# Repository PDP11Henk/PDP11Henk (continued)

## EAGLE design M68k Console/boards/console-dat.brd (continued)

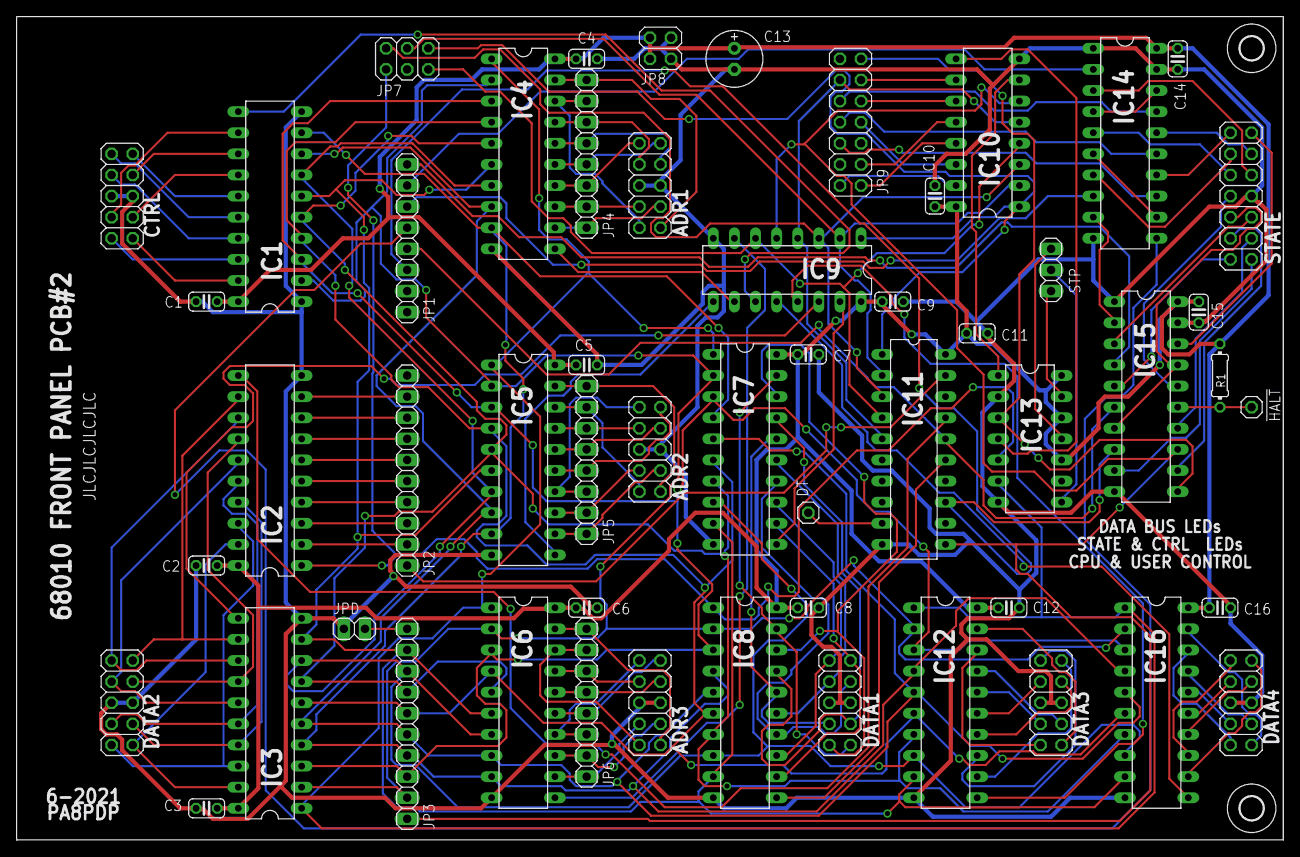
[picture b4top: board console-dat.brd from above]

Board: 2 copper layers, 152.4 x 99.1 mm, 57 parts (0 on the bottom side), 141 nets.

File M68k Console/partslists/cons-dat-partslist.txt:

Partlist

Exported from console-dat.sch at 14-6-2021 21:06

EAGLE Version 7.6.0 Copyright (c) 1988-2016 CadSoft

Assembly variant: 

Part     Value          Device          Package      Library  Sheet

!HALT    !HALT          PINHD-1X1       1X01         pinhead  4
ADR1     ADR1           PINHD-2X5       2X05         pinhead  4
ADR2     ADR2           PINHD-2X5       2X05         pinhead  4
ADR3     ADR3           PINHD-2X5       2X05         pinhead  4
C1       100n           C-EU025-024X044 C025-024X044 rcl      2
C2       100n           C-EU025-024X044 C025-024X044 rcl      2
C3       100n           C-EU025-024X044 C025-024X044 rcl      2
C4       100n           C-EU025-024X044 C025-024X044 rcl      2
C5       100n           C-EU025-024X044 C025-024X044 rcl      2
C6       100n           C-EU025-024X044 C025-024X044 rcl      2
C7       100n           C-EU025-024X044 C025-024X044 rcl      2
C8       100n           C-EU025-024X044 C025-024X044 rcl      2
C9       100n           C-EU025-024X044 C025-024X044 rcl      2
C10      100n           C-EU025-024X044 C025-024X044 rcl      1
C11      220n           C-EU025-024X044 C025-024X044 rcl      2
C12      100n           C-EU025-024X044 C025-024X044 rcl      2
C13      470µF          CPOL-EUE2.5-7   E2,5-7       rcl      1
C14      100n           C-EU025-024X044 C025-024X044 rcl      2
C15      100n           C-EU025-024X044 C025-024X044 rcl      2
C16      100n           C-EU025-024X044 C025-024X044 rcl      2
CTRL     CTRL           PINHD-2X5       2X05         pinhead  4
DATA1    DATA1          PINHD-2X5       2X05         pinhead  2
DATA2    DATA2          PINHD-2X5       2X05         pinhead  2
DATA3    DATA3          PINHD-2X5       2X05         pinhead  2
DATA4    DATA4          PINHD-2X5       2X05         pinhead  2
DT       DT             PINHD-1X1       1X01         pinhead  1
IC1      74HCT574N      74HCT574N       DIL20        74xx-eu  4
IC2      74HCT574N      74HCT574N       DIL20        74xx-eu  2
IC3      74HCT574N      74HCT574N       DIL20        74xx-eu  2
IC4      74HCT574N      74HCT574N       DIL20        74xx-eu  4
IC5      74HCT574N      74HCT574N       DIL20        74xx-eu  4
IC6      74HCT574N      74HCT574N       DIL20        74xx-eu  4
IC7      74HCT574N      74HCT574N       DIL20        74xx-eu  2
IC8      74HCT574N      74HCT574N       DIL20        74xx-eu  2
IC9      74LS138N       74LS138N        DIL16        74xx-eu  3
IC10     74LS138N       74LS138N        DIL16        74xx-eu  3
IC11     ATF16V8BP3     ATF16V8BP3      DIL20        atmel    3
IC12     74HCT574N      74HCT574N       DIL20        74xx-eu  2
IC13     74LS74N        74LS74N         DIL14        74xx-eu  3
IC14     74LS240N       74LS240N        DIL20        74xx-eu  4
IC15     74LS240N       74LS240N        DIL20        74xx-eu  4
IC16     74HCT574N      74HCT574N       DIL20        74xx-eu  2
JP1      JP1            PINHD-1X8       1X08         pinhead  1
JP2      JP2            PINHD-1X10      1X10         pinhead  1
JP3      JP3            PINHD-1X10      1X10         pinhead  1
JP4      JP4            PINHD-1X8       1X08         pinhead  1
JP5      JP5            PINHD-1X8       1X08         pinhead  1
JP6      JP6            PINHD-1X8       1X08         pinhead  1
JP7      JP7            PINHD-2X3       2X03         pinhead  1
JP8      JP8            PINHD-2X2       2X02         pinhead  1
JP9      JP9            PINHD-2X7       2X07         pinhead  1
JPD      JPD            PINHD-1X2       1X02         pinhead  1
R1       10k            R-EU_0204/7     0204/7       rcl      4
STATE    STATE          PINHD-2X7       2X07         pinhead  4
STP      STP            PINHD-1X3       1X03         pinhead  3

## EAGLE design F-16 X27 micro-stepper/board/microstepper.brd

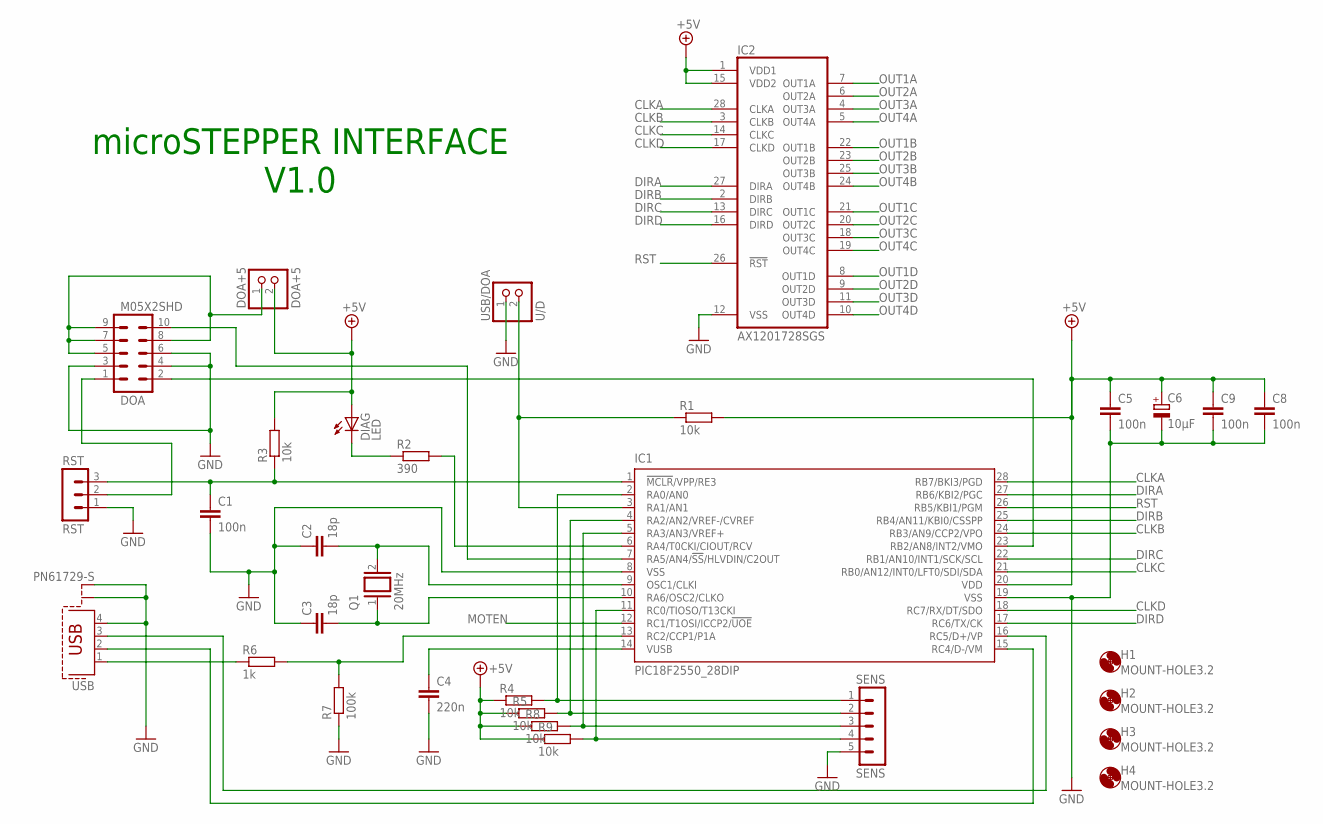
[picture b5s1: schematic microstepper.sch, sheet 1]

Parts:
C1, C5, C8, C9: 100n; C025-025X050
C2, C3: 18p; C025-025X050
C4: 220n; C5B3
C6: 10µF; E2,5-5
DIAG: LED; LED3MM
DOA: M05X2SHD; 2X5-SHROUDED
DOA+5: DOA+5; 1X02
H1, H2, H3, H4: MOUNT-HOLE3.2; 3,2
IC1: PIC18F2550_28DIP; DIL28-3
IC2: AX1201728SGS; SOP-28
Q1: 20MHz; QS
R1, R3, R4, R5, R8, R9: 10k; 0204/7
R2: 390; 0204/7
R6: 1k; 0204/7
R7: 100k; 0204/7
RST: RST; MA03-1
SENS: SENS; MA05-1
USB: PN61729-S
USB/DOA: U/D; 1X02

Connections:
+5V: C5.1, C6.+, C8.1, C9.1, DIAG.A, DOA+5.2, IC1.20 (VDD), IC2.1 (VDD1), IC2.15 (VDD2), R1.2, R3.2, R4.1, R5.1, R8.1, R9.1; also elsewhere on the board
CLKA: IC1.28 (RB7/BKI3/PGD), IC2.28 (CLKA)
CLKB: IC1.24 (RB3/AN9/CCP2/VPO), IC2.3 (CLKB)
CLKC: IC1.21 (RB0/AN12/INT0/LFT0/SDI/SDA), IC2.14 (CLKC)
CLKD: IC1.18 (RC7/RX/DT/SDO), IC2.17 (CLKD)
DIRA: IC1.27 (RB6/KBI2/PGC), IC2.27 (DIRA)
DIRB: IC1.25 (RB4/AN11/KBI0/CSSPP), IC2.2 (DIRB)
DIRC: IC1.22 (RB1/AN10/INT1/SCK/SCL), IC2.13 (DIRC)
DIRD: IC1.17 (RC6/TX/CK), IC2.16 (DIRD)
GND: C1.2, C2.1, C3.1, C4.2, C5.2, C6.-, C8.2, C9.2, DOA.3, DOA.4, DOA.6, IC1.8 (VSS), IC1.19 (VSS), IC2.12 (VSS), R7.1, RST.1, SENS.5, USB.4, USB.S1, USB.S2, USB/DOA.1; also elsewhere on the board
MOTEN: IC1.12 (RC1/T1OSI/ICCP2/!UOE); also elsewhere on the board
unnamed: IC1.11 (RC0/TIOSO/T13CKI), R9.2, SENS.4
unnamed: IC1.5 (RA3/AN3/VREF+), R8.2, SENS.3
unnamed: IC1.4 (RA2/AN2/VREF-/CVREF), R5.2, SENS.2
unnamed: IC1.2 (RA0/AN0), R4.2, SENS.1
unnamed: C4.1, IC1.14 (VUSB)
unnamed: IC1.16 (RC5/D+/VP), USB.3
unnamed: IC1.15 (RC4/D-/VM), USB.2
unnamed: R6.1, USB.1
unnamed: IC1.13 (RC2/CCP1/P1A), R6.2, R7.2
unnamed: DOA.1, RST.2
unnamed: C3.2, IC1.10 (RA6/OSC2/CLKO), Q1.1
unnamed: C2.2, IC1.9 (OSC1/CLKI), Q1.2
unnamed: C1.1, IC1.1 (!MCLR!/VPP/RE3), R3.1, RST.3
unnamed: DOA.5, DOA.7, DOA.8, DOA.9, DOA+5.1
unnamed: DOA.2, IC1.23 (RB2/AN8/INT2/VMO)
unnamed: DIAG.K (C), R2.1
unnamed: IC1.6 (RA4/T0CKI/CIOUT/RCV), R2.2
unnamed: DOA.10, IC1.7 (RA5/AN4/!SS!/HLVDIN/C2OUT)
unnamed: IC1.3 (RA1/AN1), R1.1, USB/DOA.2
OUT1A: IC2.7 (OUT1A); also elsewhere on the board
OUT1B: IC2.22 (OUT1B); also elsewhere on the board
OUT1C: IC2.21 (OUT1C); also elsewhere on the board
OUT1D: IC2.8 (OUT1D); also elsewhere on the board
OUT2A: IC2.6 (OUT2A); also elsewhere on the board
OUT2B: IC2.23 (OUT2B); also elsewhere on the board
OUT2C: IC2.20 (OUT2C); also elsewhere on the board
OUT2D: IC2.9 (OUT2D); also elsewhere on the board
OUT3A: IC2.4 (OUT3A); also elsewhere on the board
OUT3B: IC2.25 (OUT3B); also elsewhere on the board
OUT3C: IC2.18 (OUT3C); also elsewhere on the board
OUT3D: IC2.11 (OUT3D); also elsewhere on the board
OUT4A: IC2.5 (OUT4A); also elsewhere on the board
OUT4B: IC2.24 (OUT4B); also elsewhere on the board
OUT4C: IC2.19 (OUT4C); also elsewhere on the board
OUT4D: IC2.10 (OUT4D); also elsewhere on the board
RST: IC1.26 (RB5/KBI1/PGM), IC2.26 (!RST)

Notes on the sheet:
microSTEPPER INTERFACE V1.0

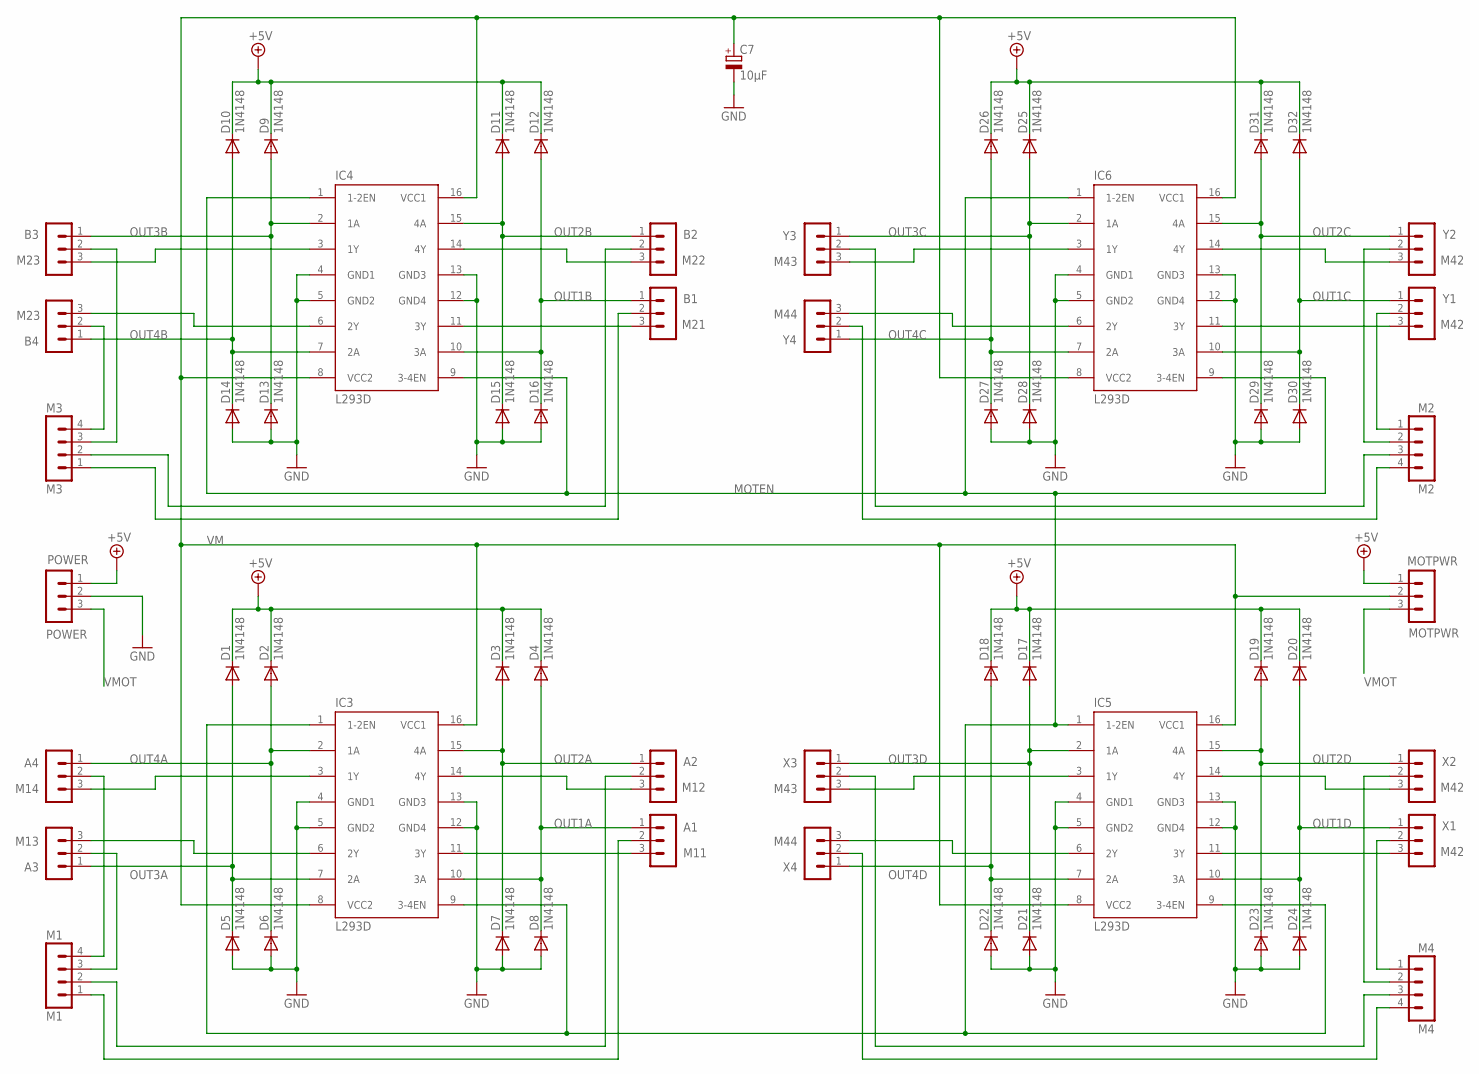
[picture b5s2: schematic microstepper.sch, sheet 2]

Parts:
A1: M11; MA03-1
A2: M12; MA03-1
A3: M13; MA03-1
A4: M14; MA03-1
B1: M21; MA03-1
B2: M22; MA03-1
B3, B4: M23; MA03-1
C7: 10µF; E2,5-5
D1, D2, D3, D4, D5, D6, D7, D8, D9, D10, D11, D12, D13, D14, D15, D16, D17, D18, D19, D20, D21, D22, D23, D24, D25, D26, D27, D28, D29, D30, D31, D32: 1N4148; DO35-7
IC3, IC4, IC5, IC6: L293D; DIL16
M1: M1; MA04-1
M2: M2; MA04-1
M3: M3; MA04-1
M4: M4; MA04-1
MOTPWR: MOTPWR; MA03-1
POWER: POWER; MA03-1
X1, X2: M42; MA03-1
X3: M43; MA03-1
X4: M44; MA03-1
Y1, Y2: M42; MA03-1
Y3: M43; MA03-1
Y4: M44; MA03-1

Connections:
+5V: D1.C, D2.C, D3.C, D4.C, D9.C, D10.C, D11.C, D12.C, D17.C, D18.C, D19.C, D20.C, D25.C, D26.C, D31.C, D32.C, MOTPWR.1, POWER.1; also elsewhere on the board
GND: C7.-, D5.A, D6.A, D7.A, D8.A, D13.A, D14.A, D15.A, D16.A, D21.A, D22.A, D23.A, D24.A, D27.A, D28.A, D29.A, D30.A, IC3.4 (GND1), IC3.5 (GND2), IC3.12 (GND4), IC3.13 (GND3), IC4.4 (GND1), IC4.5 (GND2), IC4.12 (GND4), IC4.13 (GND3), IC5.4 (GND1), IC5.5 (GND2), IC5.12 (GND4), IC5.13 (GND3), IC6.4 (GND1), IC6.5 (GND2), IC6.12 (GND4), IC6.13 (GND3), POWER.2; also elsewhere on the board
MOTEN: IC3.1 (1-2EN), IC3.9 (3-4EN), IC4.1 (1-2EN), IC4.9 (3-4EN), IC5.1 (1-2EN), IC5.9 (3-4EN), IC6.1 (1-2EN), IC6.9 (3-4EN); also elsewhere on the board
unnamed: A1.3, IC3.11 (3Y)
unnamed: A2.3, IC3.14 (4Y)
unnamed: A3.3, IC3.6 (2Y)
unnamed: A4.3, IC3.3 (1Y)
unnamed: B2.3, IC4.14 (4Y)
unnamed: B1.3, IC4.11 (3Y)
unnamed: B4.3, IC4.6 (2Y)
unnamed: B3.3, IC4.3 (1Y)
unnamed: IC5.14 (4Y), X2.3
unnamed: IC5.11 (3Y), X1.3
unnamed: IC6.14 (4Y), Y2.3
unnamed: IC5.6 (2Y), X4.3
unnamed: IC6.11 (3Y), Y1.3
unnamed: IC5.3 (1Y), X3.3
unnamed: IC6.3 (1Y), Y3.3
unnamed: IC6.6 (2Y), Y4.3
unnamed: B1.2, M3.1
unnamed: B2.2, M3.2
unnamed: B4.2, M3.4
unnamed: B3.2, M3.3
unnamed: A4.2, M1.4
unnamed: A3.2, M1.3
unnamed: A1.2, M1.1
unnamed: A2.2, M1.2
unnamed: M4.1, X1.2
unnamed: M4.2, X2.2
unnamed: M4.4, X4.2
unnamed: M4.3, X3.2
unnamed: M2.1, Y1.2
unnamed: M2.2, Y2.2
unnamed: M2.4, Y4.2
unnamed: M2.3, Y3.2
OUT1A: A1.1, D4.A, D8.C, IC3.10 (3A); also elsewhere on the board
OUT1B: B1.1, D12.A, D16.C, IC4.10 (3A); also elsewhere on the board
OUT1C: D30.C, D32.A, IC6.10 (3A), Y1.1; also elsewhere on the board
OUT1D: D20.A, D24.C, IC5.10 (3A), X1.1; also elsewhere on the board
OUT2A: A2.1, D3.A, D7.C, IC3.15 (4A); also elsewhere on the board
OUT2B: B2.1, D11.A, D15.C, IC4.15 (4A); also elsewhere on the board
OUT2C: D29.C, D31.A, IC6.15 (4A), Y2.1; also elsewhere on the board
OUT2D: D19.A, D23.C, IC5.15 (4A), X2.1; also elsewhere on the board
OUT3A: A3.1, D1.A, D5.C, IC3.7 (2A); also elsewhere on the board
OUT3B: B3.1, D9.A, D13.C, IC4.2 (1A); also elsewhere on the board
OUT3C: D25.A, D28.C, IC6.2 (1A), Y3.1; also elsewhere on the board
OUT3D: D17.A, D21.C, IC5.2 (1A), X3.1; also elsewhere on the board
OUT4A: A4.1, D2.A, D6.C, IC3.2 (1A); also elsewhere on the board
OUT4B: B4.1, D10.A, D14.C, IC4.7 (2A); also elsewhere on the board
OUT4C: D26.A, D27.C, IC6.7 (2A), Y4.1; also elsewhere on the board
OUT4D: D18.A, D22.C, IC5.7 (2A), X4.1; also elsewhere on the board
VM: C7.+, IC3.8 (VCC2), IC3.16 (VCC1), IC4.8 (VCC2), IC4.16 (VCC1), IC5.8 (VCC2), IC5.16 (VCC1), IC6.8 (VCC2), IC6.16 (VCC1), MOTPWR.2
VMOT: MOTPWR.3, POWER.3

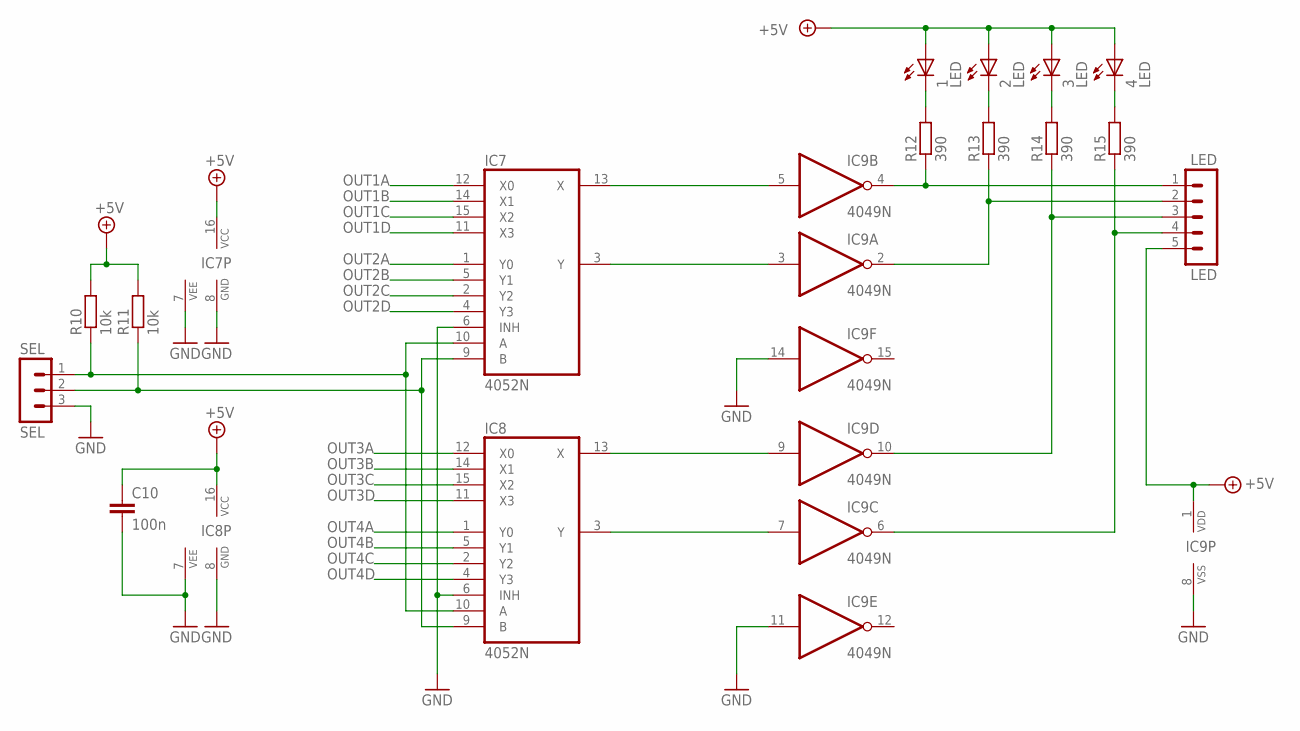
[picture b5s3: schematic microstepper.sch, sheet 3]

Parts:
1, 2, 3, 4: LED; LED3MM
C10: 100n; C025-025X050
IC7, IC8: 4052N; DIL16
IC9: 4049N; DIL16
LED: LED; MA05-1
R10, R11: 10k; 0204/7
R12, R13, R14, R15: 390; 0204/7
SEL: SEL; MA03-1

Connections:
+5V: 1.A, 2.A, 3.A, 4.A, C10.1, IC7.16 (VCC), IC8.16 (VCC), IC9.1 (VDD), LED.5, R10.2, R11.2; also elsewhere on the board
GND: C10.2, IC7.6 (INH), IC7.7 (VEE), IC7.8 (GND), IC8.6 (INH), IC8.7 (VEE), IC8.8 (GND), IC9.8 (VSS), IC9.11 (I), IC9.14 (I), SEL.3; also elsewhere on the board
unnamed: IC7.9 (B), IC8.9 (B), R11.1, SEL.2
unnamed: IC7.10 (A), IC8.10 (A), R10.1, SEL.1
unnamed: IC7.3 (Y), IC9.3 (I)
unnamed: IC7.13 (X), IC9.5 (I)
unnamed: IC8.3 (Y), IC9.7 (I)
unnamed: IC8.13 (X), IC9.9 (I)
unnamed: IC9.4 (O), LED.1, R12.1
unnamed: IC9.2 (O), LED.2, R13.1
unnamed: IC9.10 (O), LED.3, R14.1
unnamed: IC9.6 (O), LED.4, R15.1
unnamed: 1.K (C), R12.2
unnamed: 2.K (C), R13.2
unnamed: 3.K (C), R14.2
unnamed: 4.K (C), R15.2
OUT1A: IC7.12 (X0); also elsewhere on the board
OUT1B: IC7.14 (X1); also elsewhere on the board
OUT1C: IC7.15 (X2); also elsewhere on the board
OUT1D: IC7.11 (X3); also elsewhere on the board
OUT2A: IC7.1 (Y0); also elsewhere on the board
OUT2B: IC7.5 (Y1); also elsewhere on the board
OUT2C: IC7.2 (Y2); also elsewhere on the board
OUT2D: IC7.4 (Y3); also elsewhere on the board
OUT3A: IC8.12 (X0); also elsewhere on the board
OUT3B: IC8.14 (X1); also elsewhere on the board
OUT3C: IC8.15 (X2); also elsewhere on the board
OUT3D: IC8.11 (X3); also elsewhere on the board
OUT4A: IC8.1 (Y0); also elsewhere on the board
OUT4B: IC8.5 (Y1); also elsewhere on the board
OUT4C: IC8.2 (Y2); also elsewhere on the board
OUT4D: IC8.4 (Y3); also elsewhere on the board

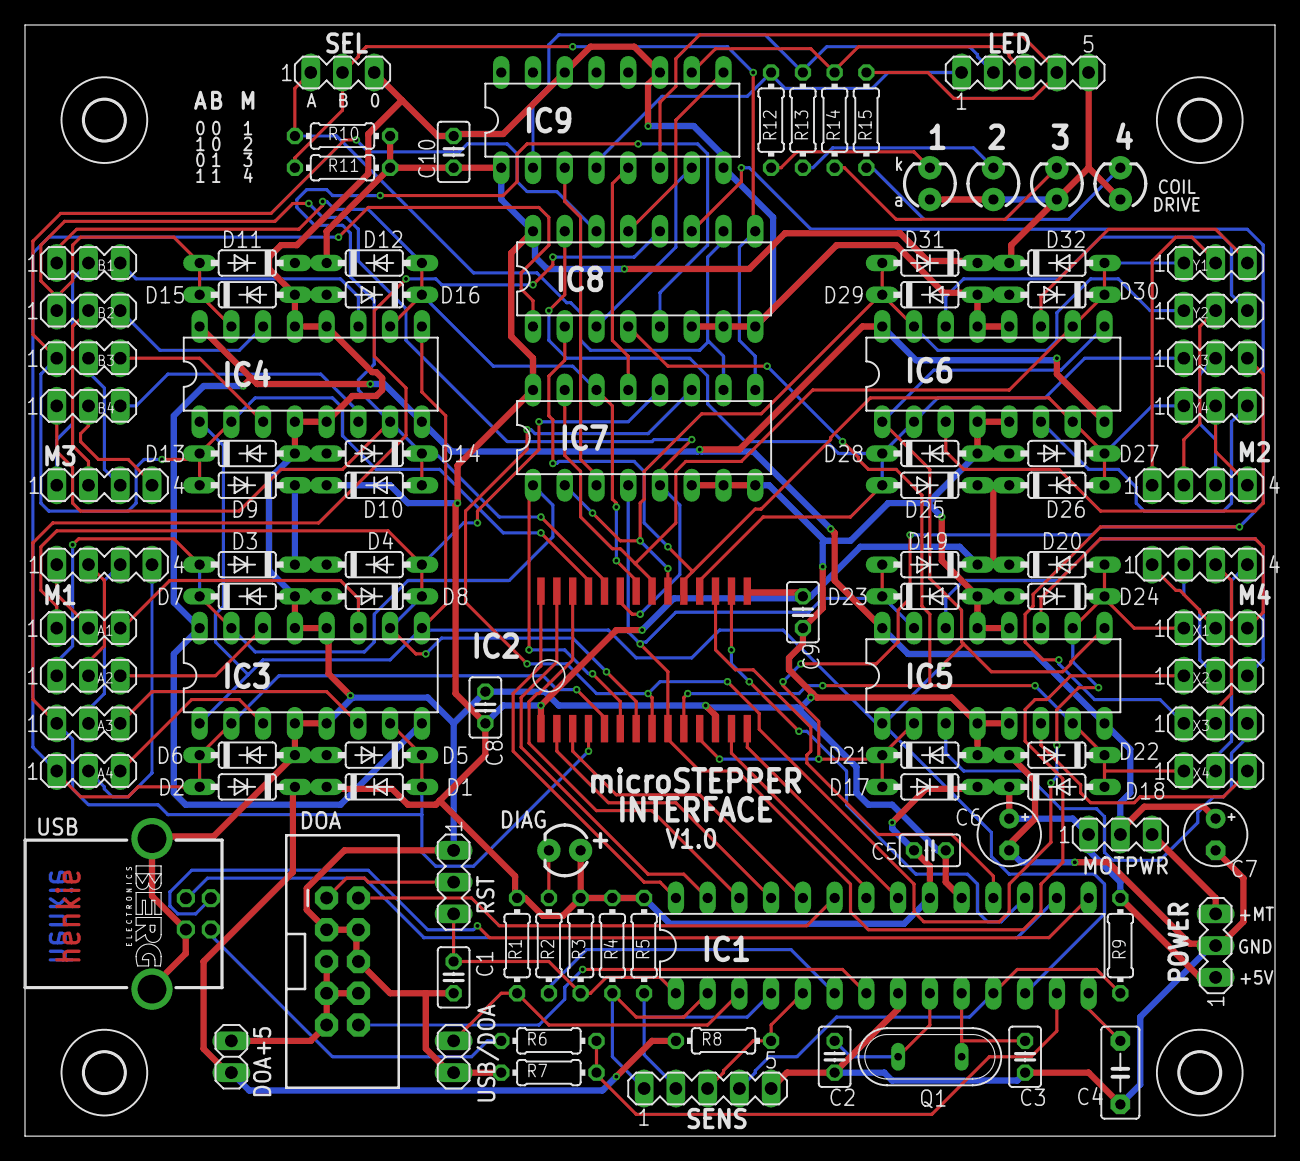
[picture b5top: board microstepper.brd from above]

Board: 2 copper layers, 100.0 x 88.9 mm, 106 parts (0 on the bottom side), 95 nets.

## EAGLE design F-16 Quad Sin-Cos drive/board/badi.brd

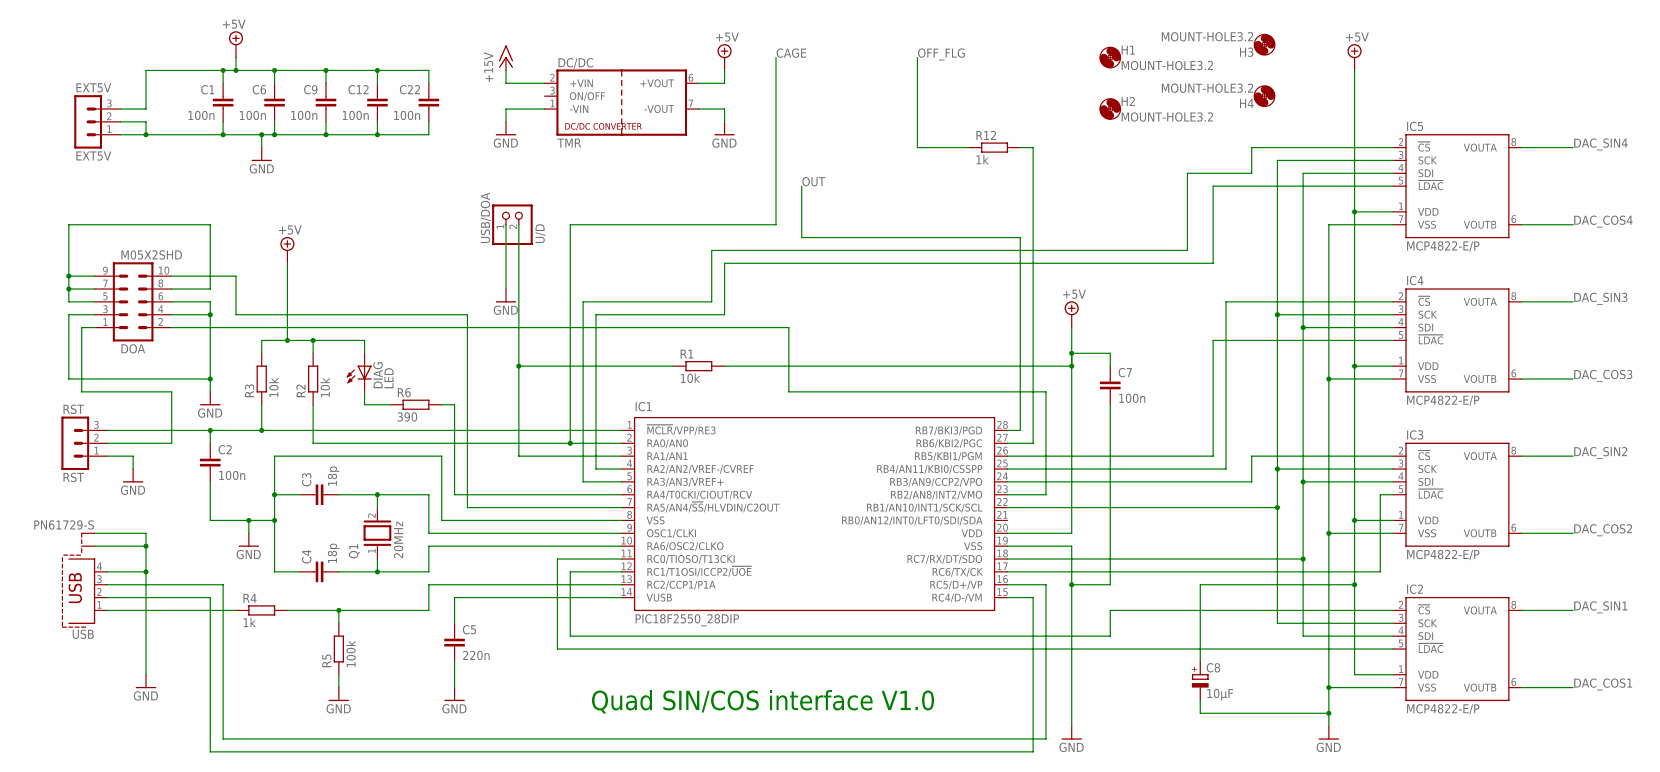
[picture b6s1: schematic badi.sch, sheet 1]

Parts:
C1, C2, C6, C7, C9, C12, C22: 100n; C025-025X050
C3, C4: 18p; C025-025X050
C5: 220n; C5B3
C8: 10µF; E2,5-5
DC/DC: TMR; TRACO_SIP-8
DIAG: LED; LED3MM
DOA: M05X2SHD; 2X5-SHROUDED
EXT5V: EXT5V; MA03-1
H1, H2, H3, H4: MOUNT-HOLE3.2; 3,2
IC1: PIC18F2550_28DIP; DIL28-3
IC2, IC3, IC4, IC5: MCP4822-E/P; DIL08
Q1: 20MHz; QS
R1, R2, R3: 10k; 0204/7
R4, R12: 1k; 0204/7
R5: 100k; 0204/7
R6: 390; 0204/7
RST: RST; MA03-1
USB: PN61729-S
USB/DOA: U/D; 1X02

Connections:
+5V: C1.1, C6.1, C7.1, C8.+, C9.1, C12.1, C22.1, DC/DC.6 (+VOUT), DIAG.A, EXT5V.3, IC1.20 (VDD), IC2.1 (VDD), IC3.1 (VDD), IC4.1 (VDD), IC5.1 (VDD), R1.2, R2.2, R3.2
+15V: DC/DC.2 (+VIN); also elsewhere on the board
CAGE: IC1.2 (RA0/AN0), R2.1; also elsewhere on the board
DAC_COS1: IC2.6 (VOUTB); also elsewhere on the board
DAC_COS2: IC3.6 (VOUTB); also elsewhere on the board
DAC_COS3: IC4.6 (VOUTB); also elsewhere on the board
DAC_COS4: IC5.6 (VOUTB); also elsewhere on the board
DAC_SIN1: IC2.8 (VOUTA); also elsewhere on the board
DAC_SIN2: IC3.8 (VOUTA); also elsewhere on the board
DAC_SIN3: IC4.8 (VOUTA); also elsewhere on the board
DAC_SIN4: IC5.8 (VOUTA); also elsewhere on the board
GND: C1.2, C2.2, C3.1, C4.1, C5.2, C6.2, C7.2, C8.-, C9.2, C12.2, C22.2, DC/DC.1 (-VIN), DC/DC.7 (-VOUT), DOA.3, DOA.4, DOA.6, EXT5V.1, EXT5V.2, IC1.8 (VSS), IC1.19 (VSS), IC2.7 (VSS), IC3.7 (VSS), IC4.7 (VSS), IC5.7 (VSS), R5.1, RST.1, USB.4, USB.S1, USB.S2, USB/DOA.1; also elsewhere on the board
unnamed: IC1.12 (RC1/T1OSI/ICCP2/!UOE), IC2.2 (!CS)
unnamed: IC1.11 (RC0/TIOSO/T13CKI), IC2.5 (!LDAC)
unnamed: IC1.24 (RB3/AN9/CCP2/VPO), IC3.2 (!CS)
unnamed: IC1.25 (RB4/AN11/KBI0/CSSPP), IC4.2 (!CS)
unnamed: IC1.4 (RA2/AN2/VREF-/CVREF), IC5.5 (!LDAC)
unnamed: IC1.5 (RA3/AN3/VREF+), IC5.2 (!CS)
unnamed: IC1.17 (RC6/TX/CK), IC3.5 (!LDAC)
unnamed: IC1.18 (RC7/RX/DT/SDO), IC2.4 (SDI), IC3.4 (SDI), IC4.4 (SDI), IC5.4 (SDI)
unnamed: IC1.26 (RB5/KBI1/PGM), IC4.5 (!LDAC)
unnamed: IC1.27 (RB6/KBI2/PGC), R12.2
unnamed: IC1.22 (RB1/AN10/INT1/SCK/SCL), IC2.3 (SCK), IC3.3 (SCK), IC4.3 (SCK), IC5.3 (SCK)
unnamed: C5.1, IC1.14 (VUSB)
unnamed: IC1.16 (RC5/D+/VP), USB.3
unnamed: IC1.15 (RC4/D-/VM), USB.2
unnamed: R4.1, USB.1
unnamed: IC1.13 (RC2/CCP1/P1A), R4.2, R5.2
unnamed: DOA.1, RST.2
unnamed: C4.2, IC1.10 (RA6/OSC2/CLKO), Q1.1
unnamed: C3.2, IC1.9 (OSC1/CLKI), Q1.2
unnamed: C2.1, IC1.1 (!MCLR!/VPP/RE3), R3.1, RST.3
unnamed: DOA.5, DOA.7, DOA.8, DOA.9
unnamed: DOA.2, IC1.23 (RB2/AN8/INT2/VMO)
unnamed: DIAG.K (C), R6.1
unnamed: IC1.6 (RA4/T0CKI/CIOUT/RCV), R6.2
unnamed: DOA.10, IC1.7 (RA5/AN4/!SS!/HLVDIN/C2OUT)
unnamed: IC1.3 (RA1/AN1), R1.1, USB/DOA.2
OFF_FLG: R12.1; also elsewhere on the board
OUT: IC1.28 (RB7/BKI3/PGD); also elsewhere on the board

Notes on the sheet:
Quad SIN/COS interface V1.0

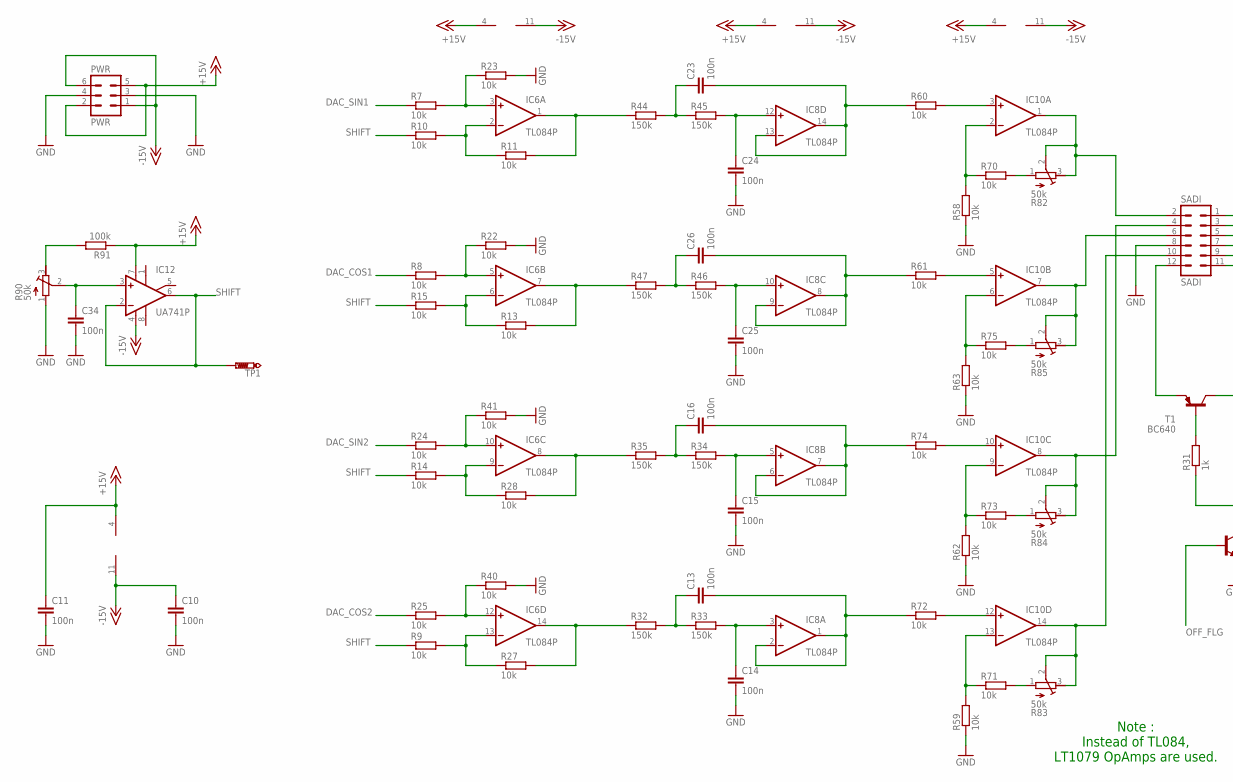
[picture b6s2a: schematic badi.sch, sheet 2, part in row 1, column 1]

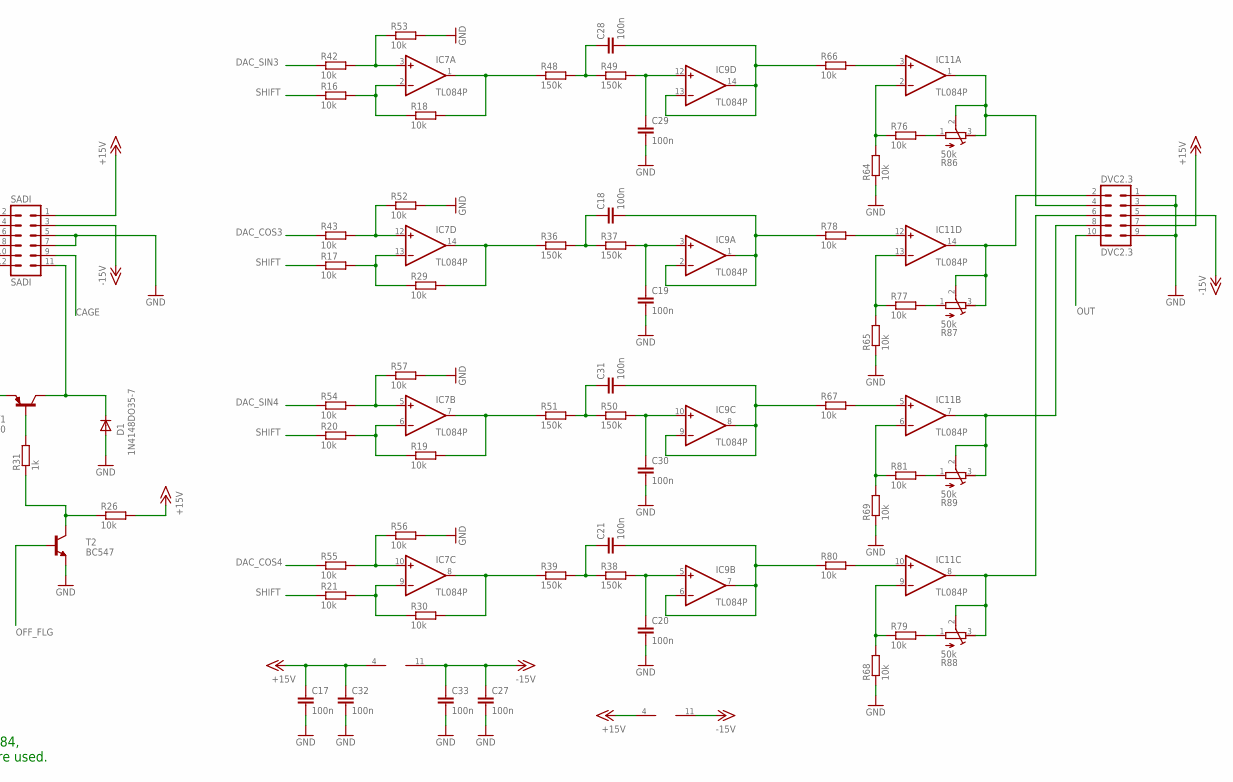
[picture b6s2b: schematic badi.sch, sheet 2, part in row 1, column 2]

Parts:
C10, C11, C13, C14, C15, C16, C17, C18, C19, C20, C21, C23, C24, C25, C26, C27, C28, C29, C30, C31, C32, C33, C34: 100n; C025-025X050
D1: 1N4148DO35-7; DO35-7
DVC2.3: DVC2.3; MA05-2
IC6, IC7, IC8, IC9, IC10, IC11: TL084P; DIL14
IC12: UA741P; DIL08
PWR: PWR; MA03-2
R7, R8, R9, R10, R11, R13, R14, R15, R16, R17, R18, R19, R20, R21, R22, R23, R24, R25, R26, R27, R28, R29, R30, R40, R41, R42, R43, R52, R53, R54, R55, R56, R57, R58, R59, R60, R61, R62, R63, R64, R65, R66, R67, R68, R69, R70, R71, R72, R73, R74, R75, R76, R77, R78, R79, R80, R81: 10k; 0204/7
R31: 1k; 0204/7
R32, R33, R34, R35, R36, R37, R38, R39, R44, R45, R46, R47, R48, R49, R50, R51: 150k; 0204/7
R82, R83, R84, R85, R86, R87, R88, R89, R90: 50k; RTRIM64Z
R91: 100k; 0204/7
SADI: SADI; MA06-2
T1: BC640; TO92-BCE
T2: BC547; TO92-CBE
TP1: PTR1B1,27; B1,27

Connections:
+15V: C11.1, C17.1, C32.1, DVC2.3.7, IC6.4 (V+), IC7.4 (V+), IC8.4 (V+), IC9.4 (V+), IC10.4 (V+), IC11.4 (V+), IC12.7 (V+), PWR.2, PWR.5, R26.2, R91.1, SADI.1; also elsewhere on the board
-15V: C10.1, C27.1, C33.1, DVC2.3.5, IC6.11 (V-), IC7.11 (V-), IC8.11 (V-), IC9.11 (V-), IC10.11 (V-), IC11.11 (V-), IC12.4 (V-), PWR.1, PWR.6, SADI.3
CAGE: SADI.9; also elsewhere on the board
DAC_COS1: R8.1; also elsewhere on the board
DAC_COS2: R25.1; also elsewhere on the board
DAC_COS3: R43.1; also elsewhere on the board
DAC_COS4: R55.1; also elsewhere on the board
DAC_SIN1: R7.1; also elsewhere on the board
DAC_SIN2: R24.1; also elsewhere on the board
DAC_SIN3: R42.1; also elsewhere on the board
DAC_SIN4: R54.1; also elsewhere on the board
GND: C10.2, C11.2, C14.2, C15.2, C17.2, C19.2, C20.2, C24.2, C25.2, C27.2, C29.2, C30.2, C32.2, C33.2, C34.2, D1.A, DVC2.3.1, DVC2.3.3, DVC2.3.9, PWR.3, PWR.4, R22.2, R23.2, R40.2, R41.2, R52.2, R53.2, R56.2, R57.2, R58.1, R59.1, R62.1, R63.1, R64.1, R65.1, R68.1, R69.1, R90.1 (A), SADI.5, SADI.7, SADI.8, T2.E; also elsewhere on the board
unnamed: IC6.3 (+IN), R7.2, R23.1
unnamed: IC6.1 (OUT), R11.2, R44.1
unnamed: IC6.5 (+IN), R8.2, R22.1
unnamed: C13.1, R32.2, R33.1
unnamed: C14.1, IC8.3 (+IN), R33.2
unnamed: C13.2, IC8.1 (OUT), IC8.2 (-IN), R72.1
unnamed: C23.1, R44.2, R45.1
unnamed: C23.2, IC8.13 (-IN), IC8.14 (OUT), R60.1
unnamed: IC6.6 (-IN), R13.1, R15.2
unnamed: IC6.7 (OUT), R13.2, R47.1
unnamed: IC6.10 (+IN), R24.2, R41.1
unnamed: C24.1, IC8.12 (+IN), R45.2
unnamed: C28.1, R48.2, R49.1
unnamed: SADI.12, T1.E
unnamed: IC6.9 (-IN), R14.2, R28.1
unnamed: C29.1, IC9.12 (+IN), R49.2
unnamed: IC6.8 (OUT), R28.2, R35.1
unnamed: IC6.12 (+IN), R25.2, R40.1
unnamed: C18.1, R36.2, R37.1
unnamed: C19.1, IC9.3 (+IN), R37.2
unnamed: C18.2, IC9.1 (OUT), IC9.2 (-IN), R78.1
unnamed: IC6.13 (-IN), R9.2, R27.1
unnamed: IC6.14 (OUT), R27.2, R32.1
unnamed: IC7.12 (+IN), R43.2, R52.1
unnamed: C28.2, IC9.13 (-IN), IC9.14 (OUT), R66.1
unnamed: C34.1, IC12.3 (+IN), R90.2 (S)
unnamed: R90.3 (E), R91.2
unnamed: D1.C, SADI.11, T1.C
unnamed: IC6.2 (-IN), R10.2, R11.1
unnamed: IC7.6 (-IN), R19.1, R20.2
unnamed: IC7.3 (+IN), R42.2, R53.1
unnamed: IC7.2 (-IN), R16.2, R18.1
unnamed: IC7.1 (OUT), R18.2, R48.1
unnamed: IC7.13 (-IN), R17.2, R29.1
unnamed: IC7.14 (OUT), R29.2, R36.1
unnamed: IC7.5 (+IN), R54.2, R57.1
unnamed: IC7.7 (OUT), R19.2, R51.1
unnamed: IC7.10 (+IN), R55.2, R56.1
unnamed: IC7.9 (-IN), R21.2, R30.1
unnamed: IC7.8 (OUT), R30.2, R39.1
unnamed: C15.1, IC8.5 (+IN), R34.2
unnamed: C16.1, R34.1, R35.2
unnamed: C16.2, IC8.6 (-IN), IC8.7 (OUT), R74.1
unnamed: C25.1, IC8.10 (+IN), R46.2
unnamed: C26.2, IC8.8 (OUT), IC8.9 (-IN), R61.1
unnamed: C26.1, R46.1, R47.2
unnamed: C30.1, IC9.10 (+IN), R50.2
unnamed: C31.1, R50.1, R51.2
unnamed: C31.2, IC9.8 (OUT), IC9.9 (-IN), R67.1
unnamed: C20.1, IC9.5 (+IN), R38.2
unnamed: C21.2, IC9.6 (-IN), IC9.7 (OUT), R80.1
unnamed: C21.1, R38.1, R39.2
unnamed: IC10.1 (OUT), R82.2 (S), R82.3 (E), SADI.2
unnamed: DVC2.3.6, IC11.8 (OUT), R88.2 (S), R88.3 (E)
unnamed: IC10.7 (OUT), R85.2 (S), R85.3 (E), SADI.6
unnamed: R26.1, R31.1, T2.C
unnamed: IC10.8 (OUT), R84.2 (S), R84.3 (E), SADI.4
unnamed: IC11.2 (-IN), R64.2, R76.1
unnamed: IC10.14 (OUT), R83.2 (S), R83.3 (E), SADI.10
unnamed: IC11.13 (-IN), R65.2, R77.1
unnamed: IC10.3 (+IN), R60.2
unnamed: IC10.5 (+IN), R61.2
unnamed: IC10.10 (+IN), R74.2
unnamed: IC10.12 (+IN), R72.2
unnamed: IC10.13 (-IN), R59.2, R71.1
unnamed: IC10.2 (-IN), R58.2, R70.1
unnamed: IC10.6 (-IN), R63.2, R75.1
unnamed: IC10.9 (-IN), R62.2, R73.1
unnamed: R71.2, R83.1 (A)
unnamed: R70.2, R82.1 (A)
unnamed: R75.2, R85.1 (A)
unnamed: R73.2, R84.1 (A)
unnamed: DVC2.3.4, IC11.1 (OUT), R86.2 (S), R86.3 (E)
unnamed: IC11.6 (-IN), R69.2, R81.1
unnamed: DVC2.3.2, IC11.14 (OUT), R87.2 (S), R87.3 (E)
unnamed: IC11.9 (-IN), R68.2, R79.1
unnamed: DVC2.3.8, IC11.7 (OUT), R89.2 (S), R89.3 (E)
unnamed: R81.2, R89.1 (A)
unnamed: R76.2, R86.1 (A)
unnamed: IC11.12 (+IN), R78.2
unnamed: IC11.3 (+IN), R66.2
unnamed: R77.2, R87.1 (A)
unnamed: R79.2, R88.1 (A)
unnamed: IC11.10 (+IN), R80.2
unnamed: IC11.5 (+IN), R67.2
unnamed: R31.2, T1.B
OFF_FLG: T2.B; also elsewhere on the board
OUT: DVC2.3.10; also elsewhere on the board
SHIFT: IC12.2 (-IN), IC12.6 (OUT), R9.1, R10.1, R14.1, R15.1, R16.1, R17.1, R20.1, R21.1, TP1.TP

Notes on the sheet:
Note : Instead of TL084, LT1079 OpAmps are used.
